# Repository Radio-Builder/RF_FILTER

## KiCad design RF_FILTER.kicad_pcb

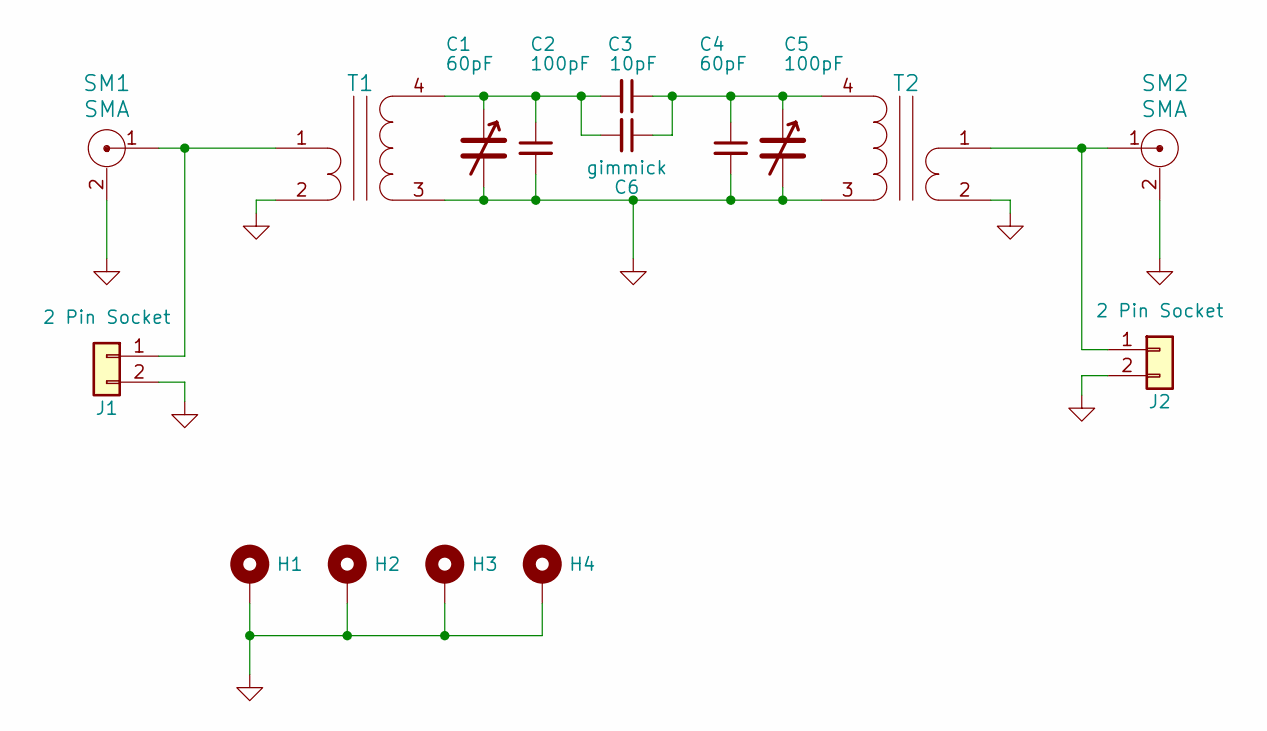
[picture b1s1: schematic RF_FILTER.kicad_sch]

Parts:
C1: 60pF; Trimmer6mm
C2: 100pF; C_1206_3216Metric_Pad1.33x1.80mm_HandSolder
C3: 10pF; C_1206_3216Metric_Pad1.33x1.80mm_HandSolder
C4: 60pF; C_1206_3216Metric_Pad1.33x1.80mm_HandSolder
C5: 100pF; Trimmer6mm
C6: gimmick; C_1206_3216Metric_Pad1.33x1.80mm_HandSolder
H1, H2, H3, H4: MountingHole_Pad; TestPoint_Plated_Hole_D3.0mm
J1, J2: 2 Pin Socket; PinHeader_1x02_P2.54mm_Vertical
SM1, SM2: SMA
T1, T2: TransLo2HiImpedance; RF-Transformer-50

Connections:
GND: C1.2, C2.2, C4.2, C5.2, H1.1, H2.1, H3.1, H4.1, J1.2, J2.2, SM1.2, SM2.2, T1.2, T1.3, T2.2, T2.3
unnamed: C1.1, C2.1, C3.2, C6.2, T1.4
unnamed: C3.1, C4.1, C5.1, C6.1, T2.4
unnamed: J1.1, SM1.1, T1.1
unnamed: J2.1, SM2.1, T2.1

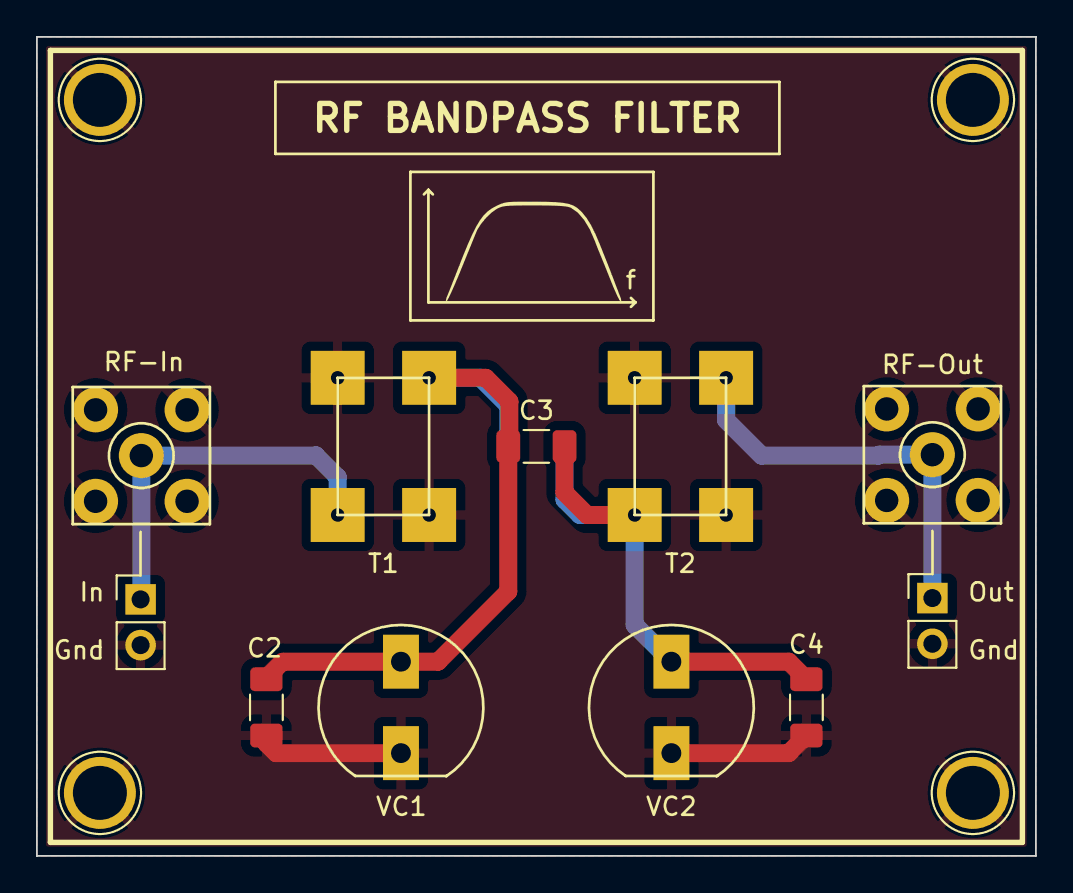
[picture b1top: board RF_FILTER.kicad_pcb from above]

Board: 2 copper layers, 55.5 x 45.5 mm, 16 parts (1 on the bottom side), 5 nets.

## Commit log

2023-05-11 1st Commit
